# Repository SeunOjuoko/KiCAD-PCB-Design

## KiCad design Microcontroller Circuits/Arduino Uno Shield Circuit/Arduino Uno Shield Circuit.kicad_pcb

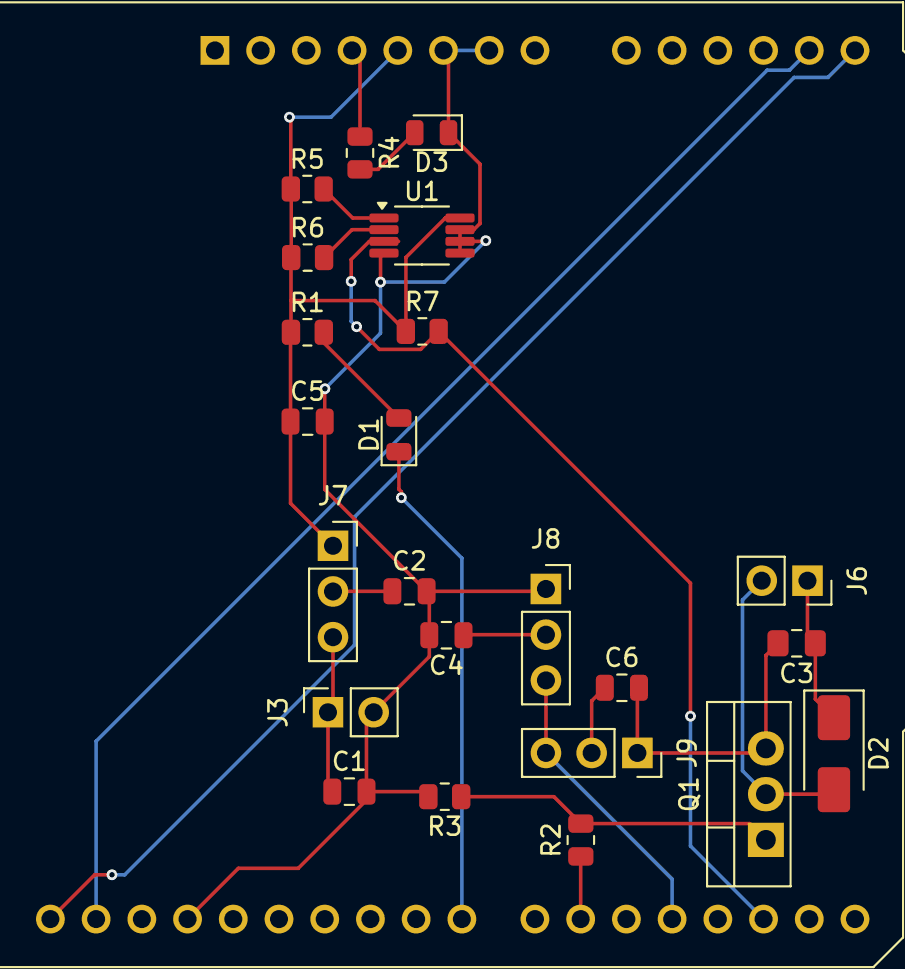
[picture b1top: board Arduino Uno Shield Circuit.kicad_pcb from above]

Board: 2 copper layers, 24 parts (0 on the bottom side), 20 nets.

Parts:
A1: Arduino_UNO_R3
C1, C4, C5, C6: 100nF; C_0805_2012Metric
C2: 100uF; C_0805_2012Metric
C3: 100nF; C_0805_2012Metric_Pad1.18x1.45mm_HandSolder
D1: LED1; LED_0805_2012Metric
D2: D; D_SMA
D3: LED2; LED_0805_2012Metric
J3, J6: Conn_01x02; PinSocket_1x02_P2.54mm_Vertical
J7, J8, J9: Conn_01x03; PinSocket_1x03_P2.54mm_Vertical
Q1: IRF540N; TO-220-3_Vertical
R1, R4: 560R; R_0805_2012Metric
R2: 0R; R_0805_2012Metric
R3, R5, R6, R7: 10K; R_0805_2012Metric
U1: TMP1075DGK; VSSOP-8_3x3mm_P0.65mm

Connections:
+3V3: A1.4 (3V3), R4.1
+5V: A1.5 (+5V), C5.1, J7.1, R1.1, R5.1, R6.1, R7.1, U1.8 (V+)
+V_EXT: C1.1, J3.1, J7.3
/A4: R5.2, U1.1 (SDA)
/A5: R6.2, U1.2 (SCL)
/D2: A1.17 (D2), R7.2, U1.3 (ALERT)
/D4: A1.19 (D4), J8.3, J9.3
/D6: A1.21 (D6), R2.1
/D8: A1.23 (D8), D1.1 (K)
/SCL/A5: A1.14 (SCL/A5), A1.32 (SCL/A5)
/SDA/A4: A1.13 (SDA/A4), A1.31 (SDA/A4)
GND: A1.6 (GND), A1.7 (GND), A1.29 (GND), C1.2, C2.2, C3.2, C4.2, C5.2, C6.2, D3.1 (K), J3.2, J8.1, J9.1, Q1.3 (S), R3.2, U1.4 (GND), U1.5 (A2), U1.6 (A1), U1.7 (A0)
unnamed: D1.2 (A), R1.2
unnamed: D2.2 (A), J6.2, Q1.2 (D)
unnamed: C3.1, D2.1 (K), J6.1
unnamed: D3.2 (A), R4.2
unnamed: C2.1, J7.2
unnamed: C4.1, J8.2
unnamed: C6.1, J9.2
unnamed: Q1.1 (G), R2.2, R3.1

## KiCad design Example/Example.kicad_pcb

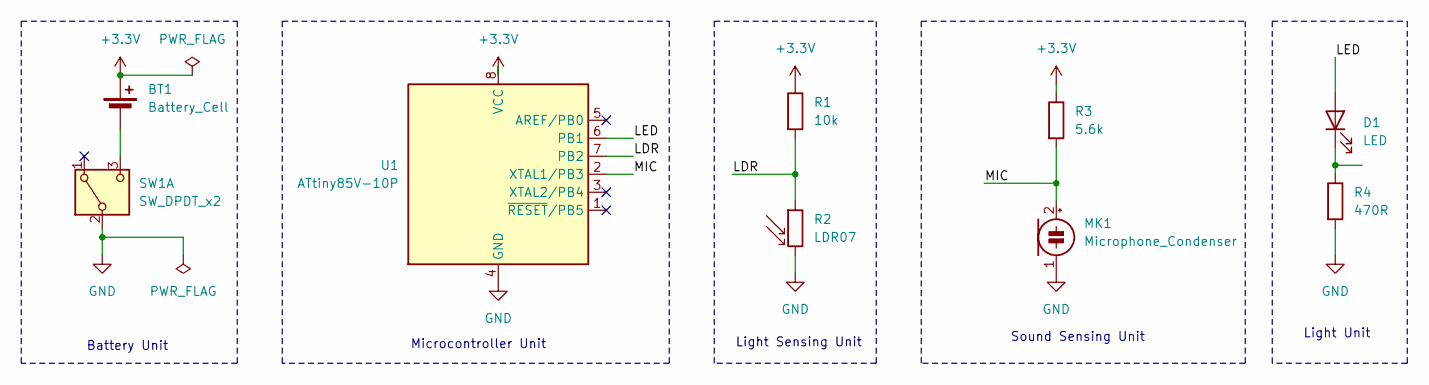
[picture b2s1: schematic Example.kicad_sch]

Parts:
BT1: Battery_Cell; BatteryHolder_ComfortableElectronic_CH273-2450_1x2450
D1: LED; LED_D5.0mm
MK1: Microphone_Condenser; PinHeader_1x02_P2.54mm_Vertical
R1: 10k; R_Axial_DIN0207_L6.3mm_D2.5mm_P15.24mm_Horizontal
R2: LDR07; R_LDR_5.1x4.3mm_P3.4mm_Vertical
R3: 5.6k; R_Axial_DIN0207_L6.3mm_D2.5mm_P15.24mm_Horizontal
R4: 470R; R_Axial_DIN0207_L6.3mm_D2.5mm_P15.24mm_Horizontal
SW1: SW_DPDT_x2; SW_CK_JS202011AQN_DPDT_Angled
U1: ATtiny85V-10P; DIP-8_W7.62mm

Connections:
+3.3V: BT1.1 (+), R1.1, R3.1, U1.8 (VCC)
/LDR: R1.2, R2.1, U1.7 (PB2)
/LED: D1.2 (A), U1.6 (PB1)
/MIC: MK1.2 (+), R3.2, U1.2 (XTAL1/PB3)
GND: MK1.1 (-), R2.2, R4.2, SW1.2 (B), U1.4 (GND)
unnamed: BT1.2 (-), SW1.3 (C)
unnamed: D1.1 (K), R4.1

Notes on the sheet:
Sound Sensing Unit
Light Sensing Unit
Battery Unit
Microcontroller Unit
Light Unit

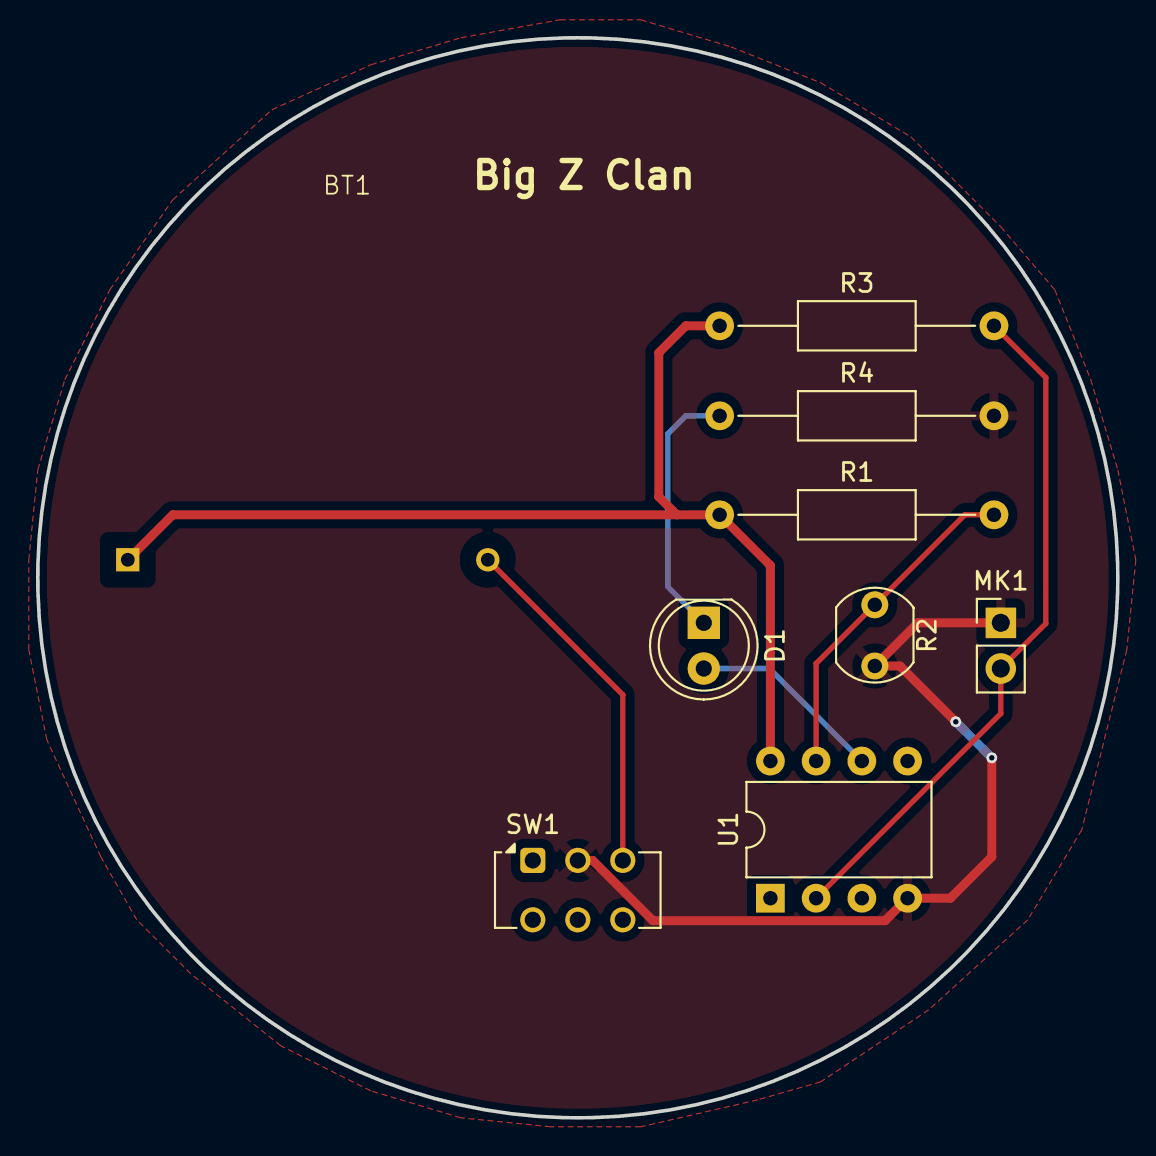
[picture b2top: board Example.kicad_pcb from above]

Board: 2 copper layers, 60.0 x 60.0 mm, 9 parts (0 on the bottom side), 7 nets.

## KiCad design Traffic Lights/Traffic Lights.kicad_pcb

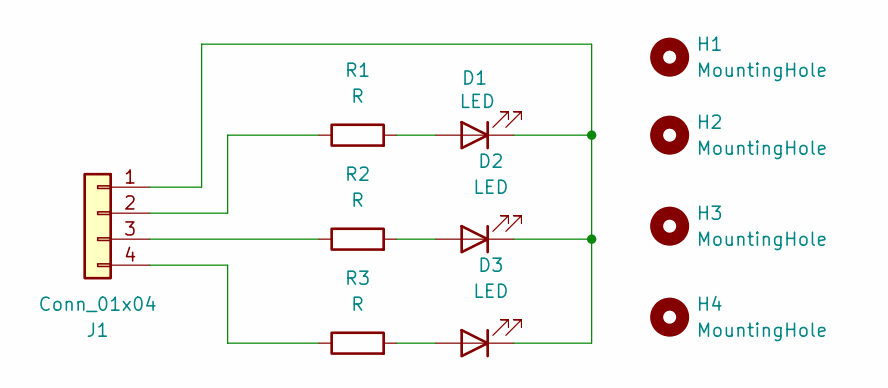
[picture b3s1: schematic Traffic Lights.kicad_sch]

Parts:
D1, D2, D3: LED; LED_D3.0mm
H1, H2, H3, H4: MountingHole; MountingHole_2.5mm_Pad
J1: Conn_01x04; PinHeader_1x04_P2.54mm_Horizontal
R1, R2, R3: R; R_Axial_DIN0204_L3.6mm_D1.6mm_P5.08mm_Vertical

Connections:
unnamed: D1.2 (A), R1.2
unnamed: D1.1 (K), D2.1 (K), D3.1 (K), J1.1
unnamed: D2.2 (A), R2.2
unnamed: D3.2 (A), R3.2
unnamed: J1.2, R1.1
unnamed: J1.3, R2.1
unnamed: J1.4, R3.1

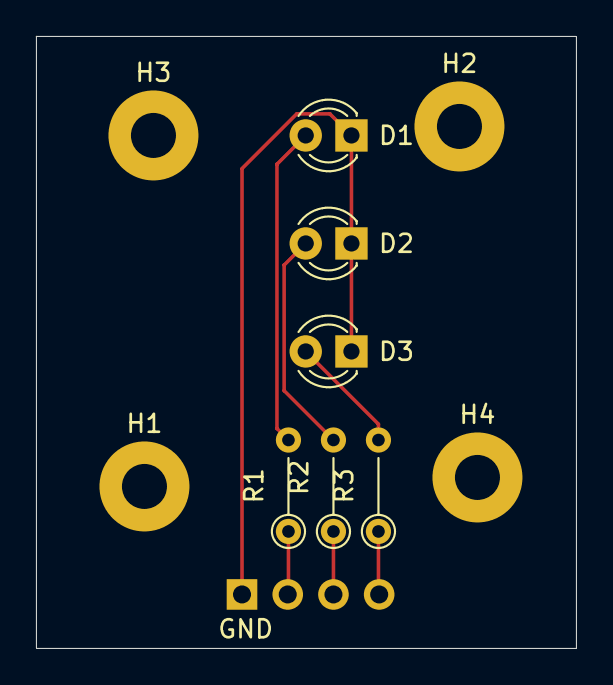
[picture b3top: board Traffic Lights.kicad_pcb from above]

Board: 2 copper layers, 30.0 x 34.0 mm, 11 parts (1 on the bottom side), 7 nets.

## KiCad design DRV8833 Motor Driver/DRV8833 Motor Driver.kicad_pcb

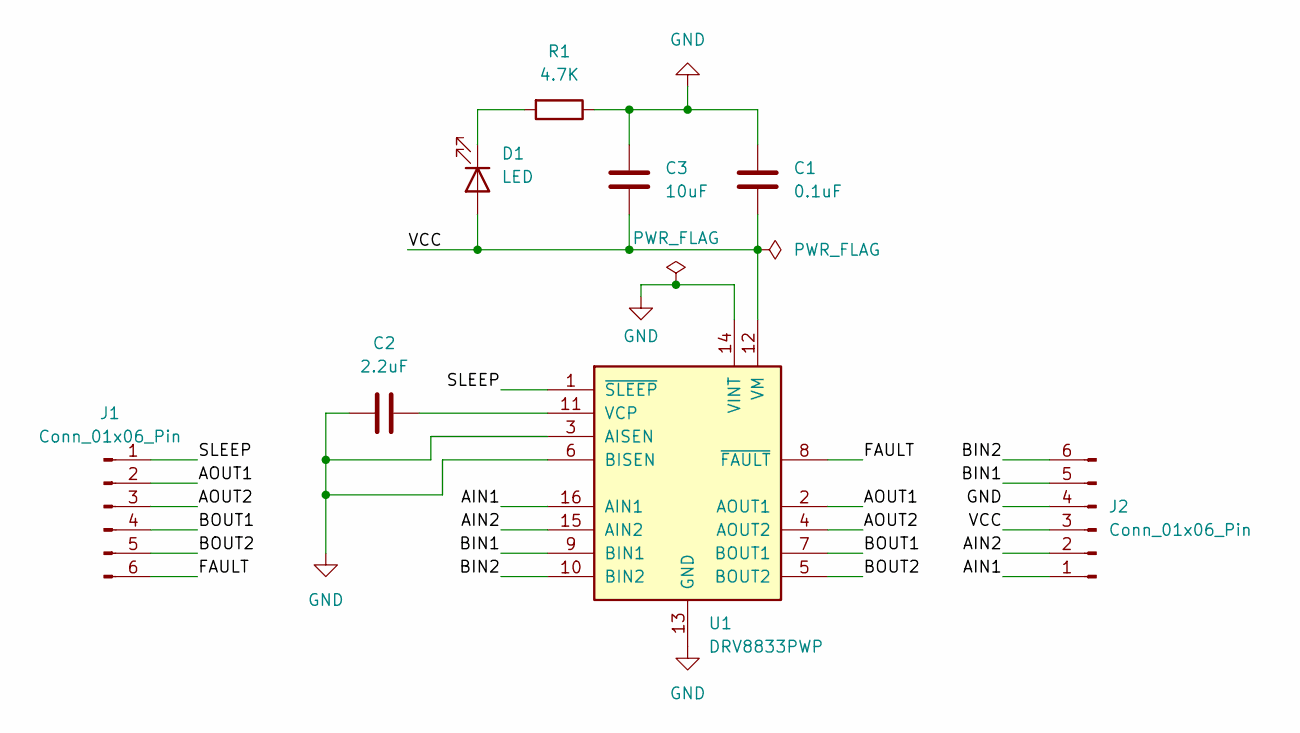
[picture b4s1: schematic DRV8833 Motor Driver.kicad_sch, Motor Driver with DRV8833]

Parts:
C1: 0.1uF; C_0805_2012Metric
C2: 2.2uF; C_0805_2012Metric
C3: 10uF; CP_EIA-6032-20_AVX-F
D1: LED; LED_0805_2012Metric
J1, J2: Conn_01x06_Pin; PinHeader_1x06_P2.54mm_Vertical
R1: 4.7K; R_0805_2012Metric
U1: DRV8833PWP; HTSSOP-16-1EP_4.4x5mm_P0.65mm_EP3.4x5mm_Mask2.46x2.31mm_The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

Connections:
/AIN1: J2.1, U1.16 (AIN1)
/AIN2: J2.2, U1.15 (AIN2)
/AOUT1: J1.2, U1.2 (AOUT1)
/AOUT2: J1.3, U1.4 (AOUT2)
/BIN1: J2.5, U1.9 (BIN1)
/BIN2: J2.6, U1.10 (BIN2)
/BOUT1: J1.4, U1.7 (BOUT1)
/BOUT2: J1.5, U1.5 (BOUT2)
/FAULT: J1.6, U1.8 (~FAULT)
/SLEEP: J1.1, U1.1 (~SLEEP)
/VCC: C1.2, C3.2, D1.2 (A), J2.3, U1.12 (VM)
GND: C1.1, C2.1, C3.1, J2.4, R1.1, U1.3 (AISEN), U1.6 (BISEN), U1.13 (GND), U1.14 (VINT), U1.17 (GND)
unnamed: D1.1 (K), R1.2
unnamed: C2.2, U1.11 (VCP)

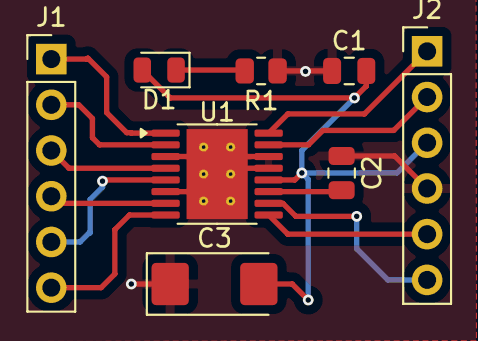
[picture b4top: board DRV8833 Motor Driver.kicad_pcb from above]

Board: 2 copper layers, 8 parts (0 on the bottom side), 14 nets.

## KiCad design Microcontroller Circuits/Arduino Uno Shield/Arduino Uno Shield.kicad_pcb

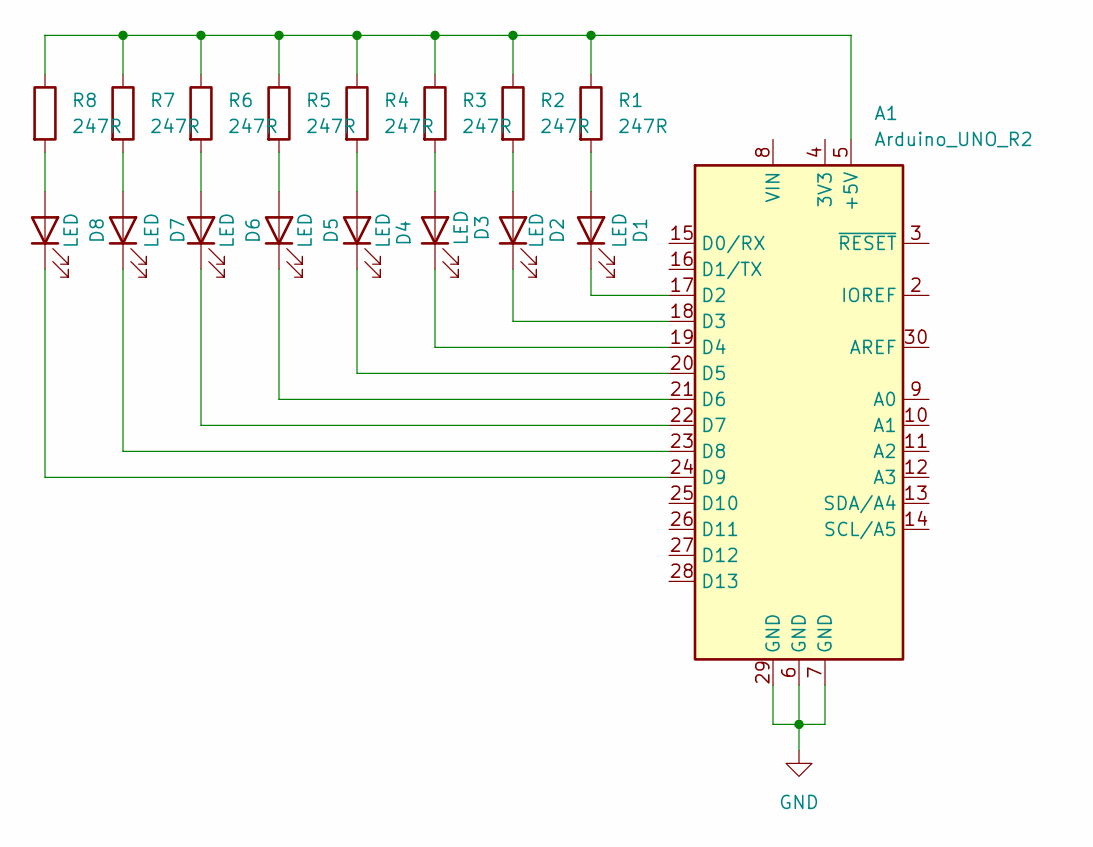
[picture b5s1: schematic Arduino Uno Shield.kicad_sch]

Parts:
A1: Arduino_UNO_R2
D1, D2, D3, D4, D5, D6, D7, D8: LED; LED_0805_2012Metric
R1, R2, R3, R4, R5, R6, R7, R8: 247R; R_0603_1608Metric

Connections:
GND: A1.6 (GND), A1.7 (GND), A1.29 (GND)
unnamed: A1.5 (+5V), R1.1, R2.1, R3.1, R4.1, R5.1, R6.1, R7.1, R8.1
unnamed: A1.17 (D2), D1.1 (K)
unnamed: A1.18 (D3), D2.1 (K)
unnamed: A1.19 (D4), D3.1 (K)
unnamed: A1.20 (D5), D4.1 (K)
unnamed: A1.21 (D6), D5.1 (K)
unnamed: A1.22 (D7), D6.1 (K)
unnamed: A1.23 (D8), D7.1 (K)
unnamed: A1.24 (D9), D8.1 (K)
unnamed: D1.2 (A), R1.2
unnamed: D2.2 (A), R2.2
unnamed: D3.2 (A), R3.2
unnamed: D4.2 (A), R4.2
unnamed: D5.2 (A), R5.2
unnamed: D6.2 (A), R6.2
unnamed: D7.2 (A), R7.2
unnamed: D8.2 (A), R8.2

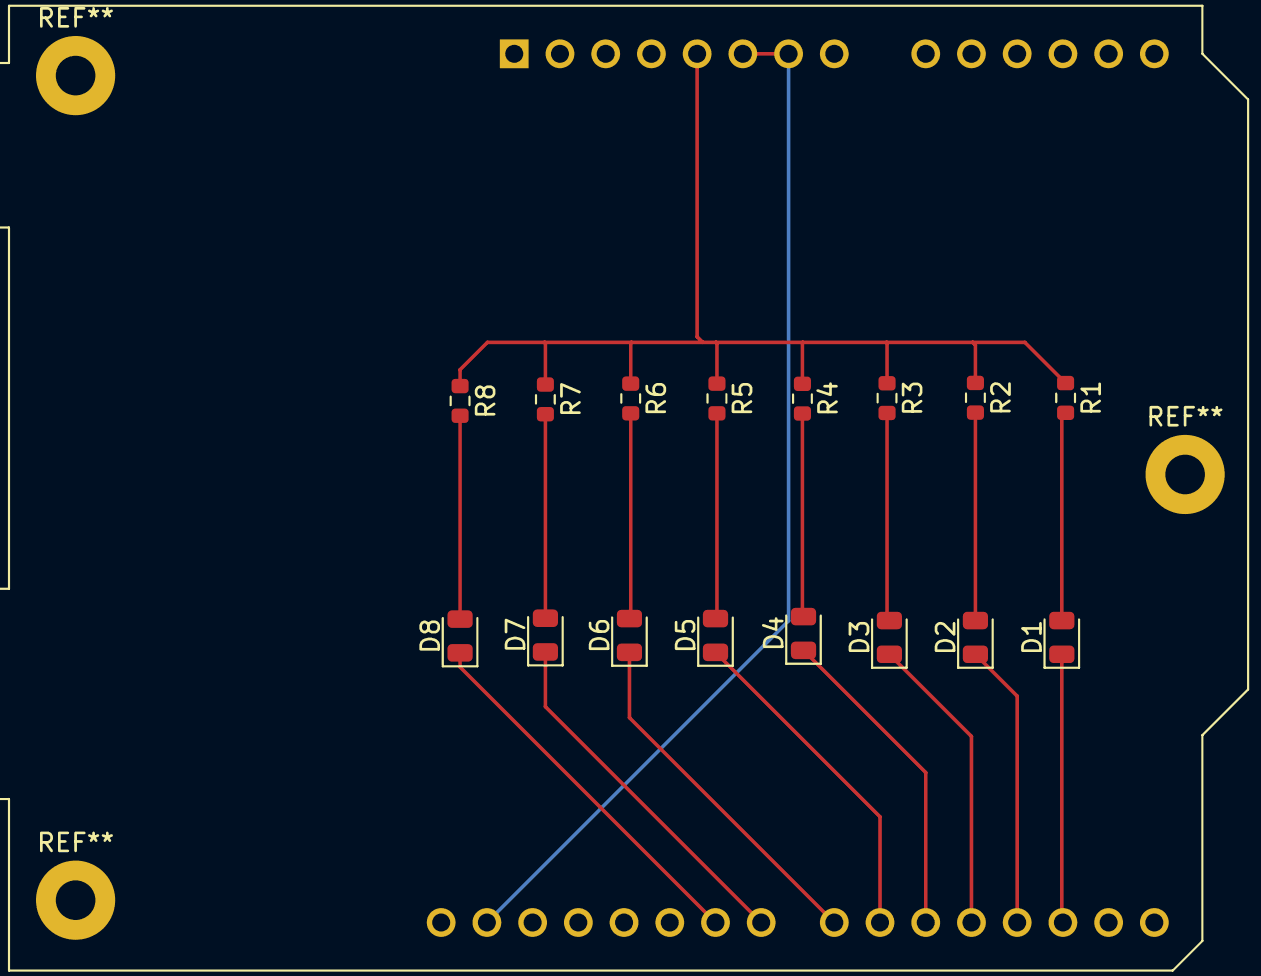
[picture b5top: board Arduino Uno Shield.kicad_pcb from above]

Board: 2 copper layers, 17 parts (0 on the bottom side), 18 nets.

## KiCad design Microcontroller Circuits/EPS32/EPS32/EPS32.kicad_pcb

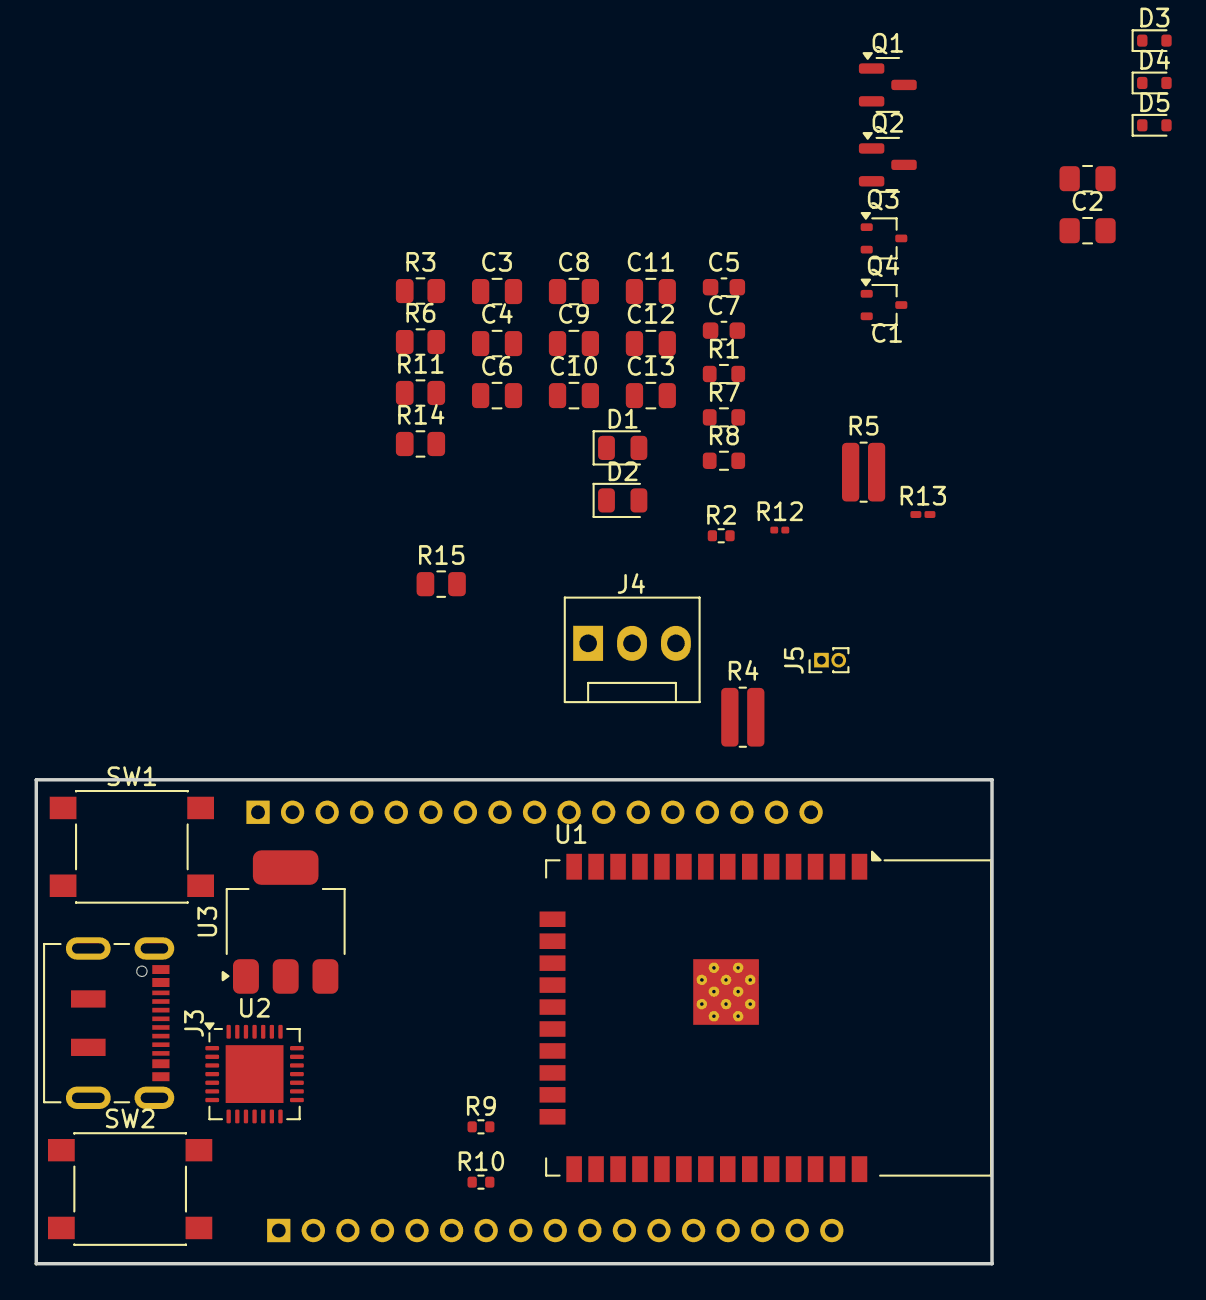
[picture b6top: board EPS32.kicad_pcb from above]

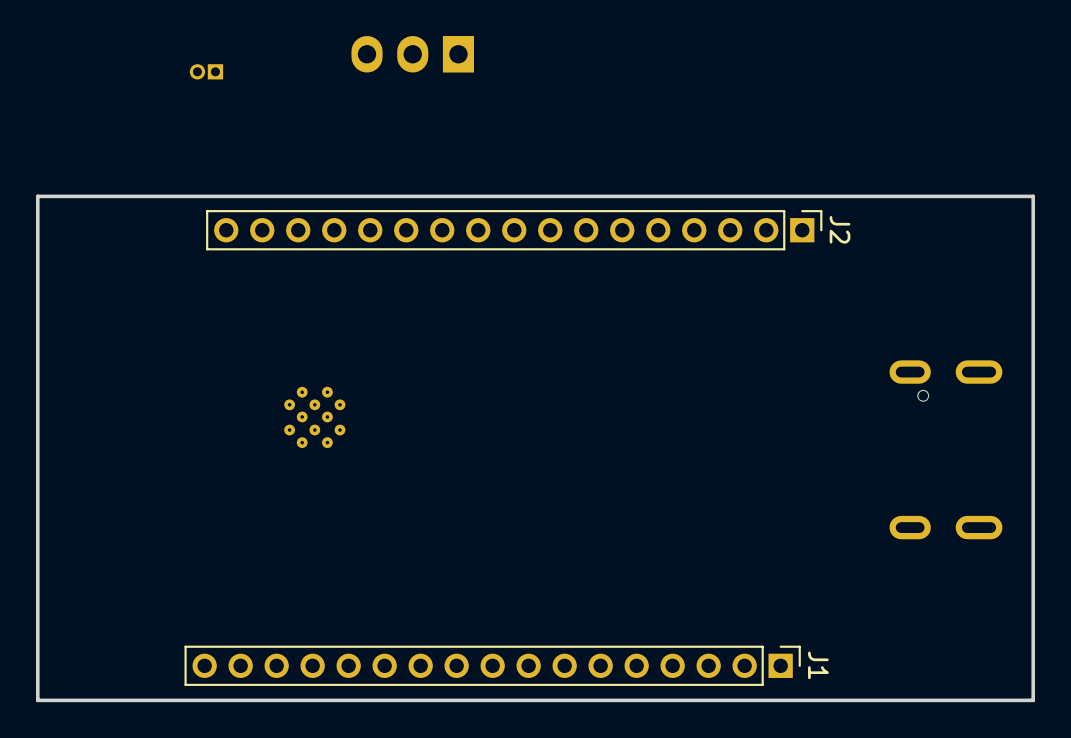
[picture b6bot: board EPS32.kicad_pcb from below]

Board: 2 copper layers, 55.3 x 28.0 mm, 47 parts (2 on the bottom side), 20 nets, no tracks yet.

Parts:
C1, C2: 10uF; C_0805_2012Metric_Pad1.18x1.45mm_HandSolder
C3, C4, C6, C8, C9, C10, C11, C12, C13: 100nF; C_0805_2012Metric
C5, C7: 4.7uF; C_0603_1608Metric
D1, D2: GREEN LED; LED_0805_2012Metric
D3, D4, D5: D_TVS; D_SOD-523
J1, J2: Conn_01x17; PinHeader_1x17_P2.00mm_Vertical
J3: Socket Type Micro B 2.0 USB; USB_C_Receptacle_JAE_DX07S016JA1R1500
J4: Conn_01x03; FanPinHeader_1x03_P2.54mm_Vertical
J5: Conn_01x02; PinHeader_1x02_P1.00mm_Vertical
Q1, Q2: 2N7002; SOT-23
Q3, Q4: BC818W; SOT-323_SC-70
R1: 5.1K; R_0603_1608Metric
R2: 560R; R_0402_1005Metric
R3, R6, R11, R14, R15: 10K; R_0805_2012Metric
R4, R5: 1K; R_0612_1632Metric
R7: 22.1K; R_0603_1608Metric
R8: 47.5K; R_0603_1608Metric
R9, R10: 22R; R_0402_1005Metric
R12: 0R; R_0201_0603Metric
R13: 0R; R_0201_0603Metric_Pad0.64x0.40mm_HandSolder
SW1, SW2: SW_Push_Dual_x2; SW_SPST_PTS645
U1: ESP32-WROOM-32E; ESP32-WROOM-32D
U2: CP2102N-Axx-xQFN28; QFN-28-1EP_5x5mm_P0.5mm_EP3.35x3.35mm
U3: AMS1117CS-3.3; SOT-223

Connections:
+3.3V: C2.1, C5.1, C6.1, C7.1, C8.1, C9.1, C11.1, J1.2, J2.1, J5.1, R1.1, R2.1, R5.1, R11.1, U1.2 (VDD), U2.6 (VDD), U2.7 (VREGIN), U3.2 (VO), U3.4 (TAB)
+5V: C1.1, J4.2, U3.3 (VI)
GND: C1.2, C2.2, C3.2, C4.2, C5.2, C6.2, C7.2, C8.2, C9.2, C10.2, C11.2, C12.2, C13.2, D1.1 (K), D3.1 (A1), D4.1 (A1), D5.1 (A1), J1.1, J1.4, J1.15, J2.2, J2.4, J2.8, J2.13, J2.15, J2.16, Q1.2 (S), Q2.2 (S), R3.2, R6.2, R8.2, SW1.1 (C), SW2.1 (C), U1.1 (GND), U1.15 (GND), U1.38 (GND), U1.39 (GND), U2.3 (GND), U2.29 (GND), U3.1 (GND)
unnamed: D1.2 (A), R1.2
unnamed: D2.2 (A), R2.2
unnamed: C3.1, D3.2 (A2)
unnamed: D4.2 (A2), Q2.3 (D)
unnamed: D5.2 (A2), Q1.3 (D)
unnamed: C10.1, J1.17
unnamed: C4.1, J5.2, Q1.1 (G), Q2.1 (G), R3.1, R4.1
unnamed: Q3.1 (B), R14.1
unnamed: Q3.2 (E), R15.2
unnamed: Q4.1 (B), R15.1
unnamed: Q4.3 (C), R14.2
unnamed: C12.1, R11.2, SW1.2 (D)
unnamed: C13.1, SW2.2 (D)
unnamed: R9.2, R10.2, U1.25 (IO0)
unnamed: R7.2, R8.1, U2.8 (VBUS)
unnamed: R5.2, U2.9 (~RST)
unnamed: R6.1, U2.11 (~SUSPEND)

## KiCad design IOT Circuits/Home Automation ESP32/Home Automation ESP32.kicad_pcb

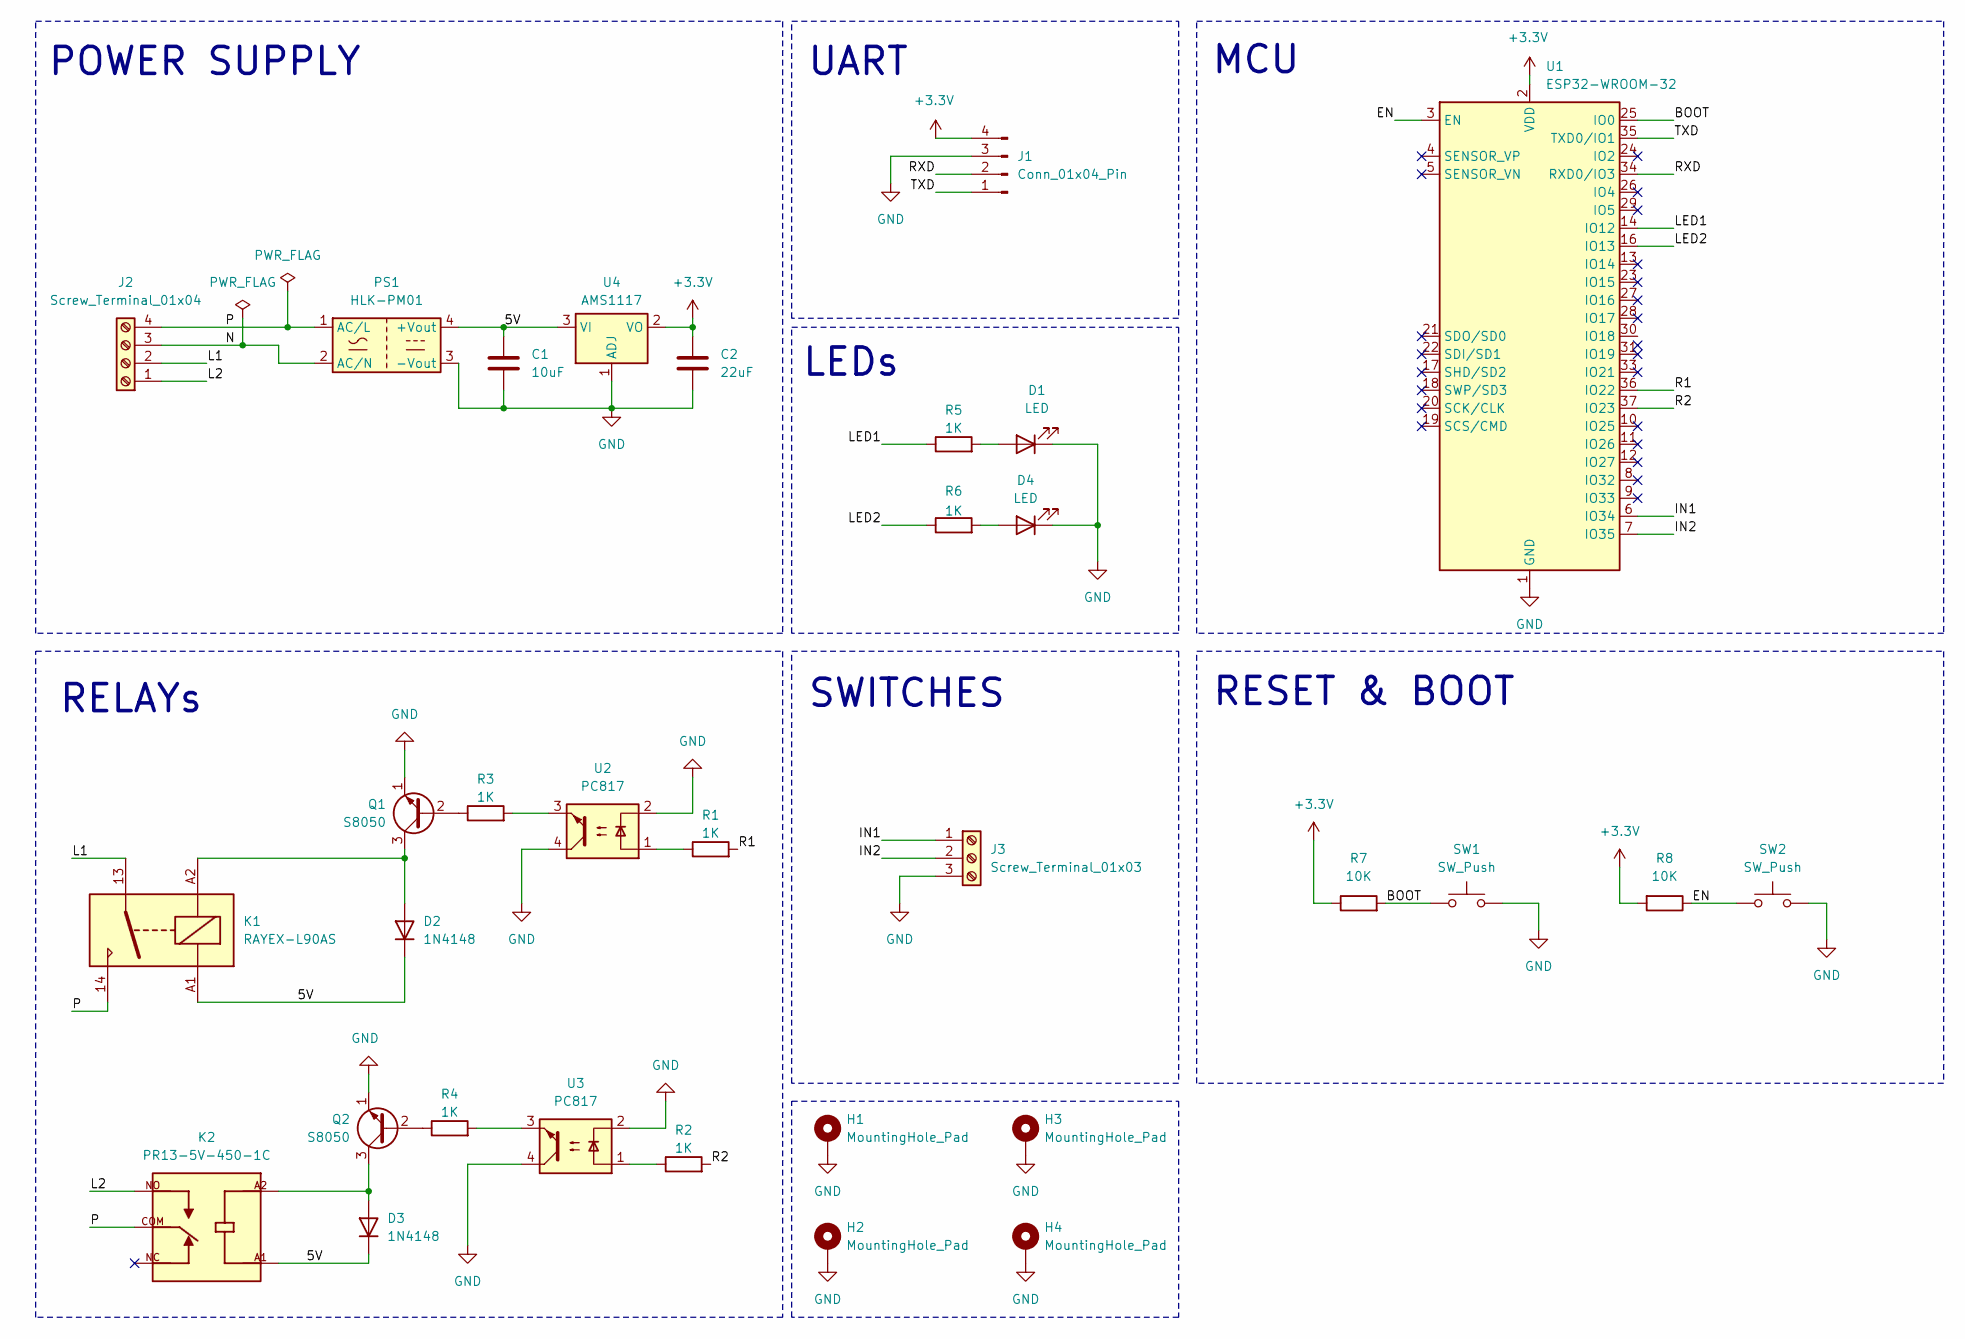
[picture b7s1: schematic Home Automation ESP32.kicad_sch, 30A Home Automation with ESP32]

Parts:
C1: 10uF; C_0805_2012Metric
C2: 22uF; C_0805_2012Metric
D1, D4: LED; LED_0805_2012Metric
D2, D3: 1N4148; D_DO-35_SOD27_P7.62mm_Horizontal
H1, H2, H3, H4: MountingHole_Pad; MountingHole_2.7mm_M2.5_Pad_Via
J1: Conn_01x04_Pin; PinHeader_1x04_P2.54mm_Vertical
J2: Screw_Terminal_01x04; TerminalBlock_bornier-4_P5.08mm
J3: Screw_Terminal_01x03; TerminalBlock_bornier-3_P5.08mm
K1: RAYEX-L90AS; Relay_SPST_RAYEX-L90AS
K2: PR13-5V-450-1C; RELAY_PR13-5V-450-1C; PARTREV 1.0
PS1: HLK-PM01; Converter_ACDC_Hi-Link_HLK-PMxx
Q1, Q2: S8050; TO-92_Inline
R1, R2, R3, R4, R5, R6: 1K; R_0805_2012Metric
R7, R8: 10K; R_0805_2012Metric
SW1, SW2: SW_Push; SW_PUSH_6mm
U1: ESP32-WROOM-32
U2, U3: PC817; DIP-4_W7.62mm
U4: AMS1117; SOT-223-3_TabPin2

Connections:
+3.3V: C2.1, J1.4, R7.1, R8.2, U1.2 (VDD), U4.2 (VO)
/5V: C1.1, D2.1 (K), D3.1 (K), K1.A1, K2.A1, PS1.4 (+Vout), U4.3 (VI)
/BOOT: R7.2, SW1.1, U1.25 (IO0)
/EN: R8.1, SW2.1, U1.3 (EN)
/IN1: J3.1, U1.6 (IO34)
/IN2: J3.2, U1.7 (IO35)
/L1: J2.2, K1.13
/L2: J2.1, K2.NO
/LED1: R5.1, U1.14 (IO12)
/LED2: R6.1, U1.16 (IO13)
/N: J2.3, PS1.2 (AC/N)
/P: J2.4, K1.14, K2.COM, PS1.1 (AC/L)
/R1: R1.2, U1.36 (IO22)
/R2: R2.2, U1.37 (IO23)
/RXD: J1.2, U1.34 (RXD0/IO3)
/TXD: J1.1, U1.35 (TXD0/IO1)
GND: C1.2, C2.2, D1.1 (K), D4.1 (K), H1.1, H2.1, H3.1, H4.1, J1.3, J3.3, PS1.3 (-Vout), Q1.1 (E), Q2.1 (E), SW1.2, SW2.2, U1.1 (GND), U1.15 (GND), U1.38 (GND), U1.39 (GND), U2.2, U2.4, U3.2, U3.4, U4.1 (ADJ)
unnamed: D1.2 (A), R5.2
unnamed: D2.2 (A), K1.A2, Q1.3 (C)
unnamed: D3.2 (A), K2.A2, Q2.3 (C)
unnamed: D4.2 (A), R6.2
unnamed: Q1.2 (B), R3.1
unnamed: Q2.2 (B), R4.1
unnamed: R1.1, U2.1
unnamed: R2.1, U3.1
unnamed: R3.2, U2.3
unnamed: R4.2, U3.3

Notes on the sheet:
POWER SUPPLY
LEDs
RESET & BOOT
SWITCHES
RELAYs
UART
MCU

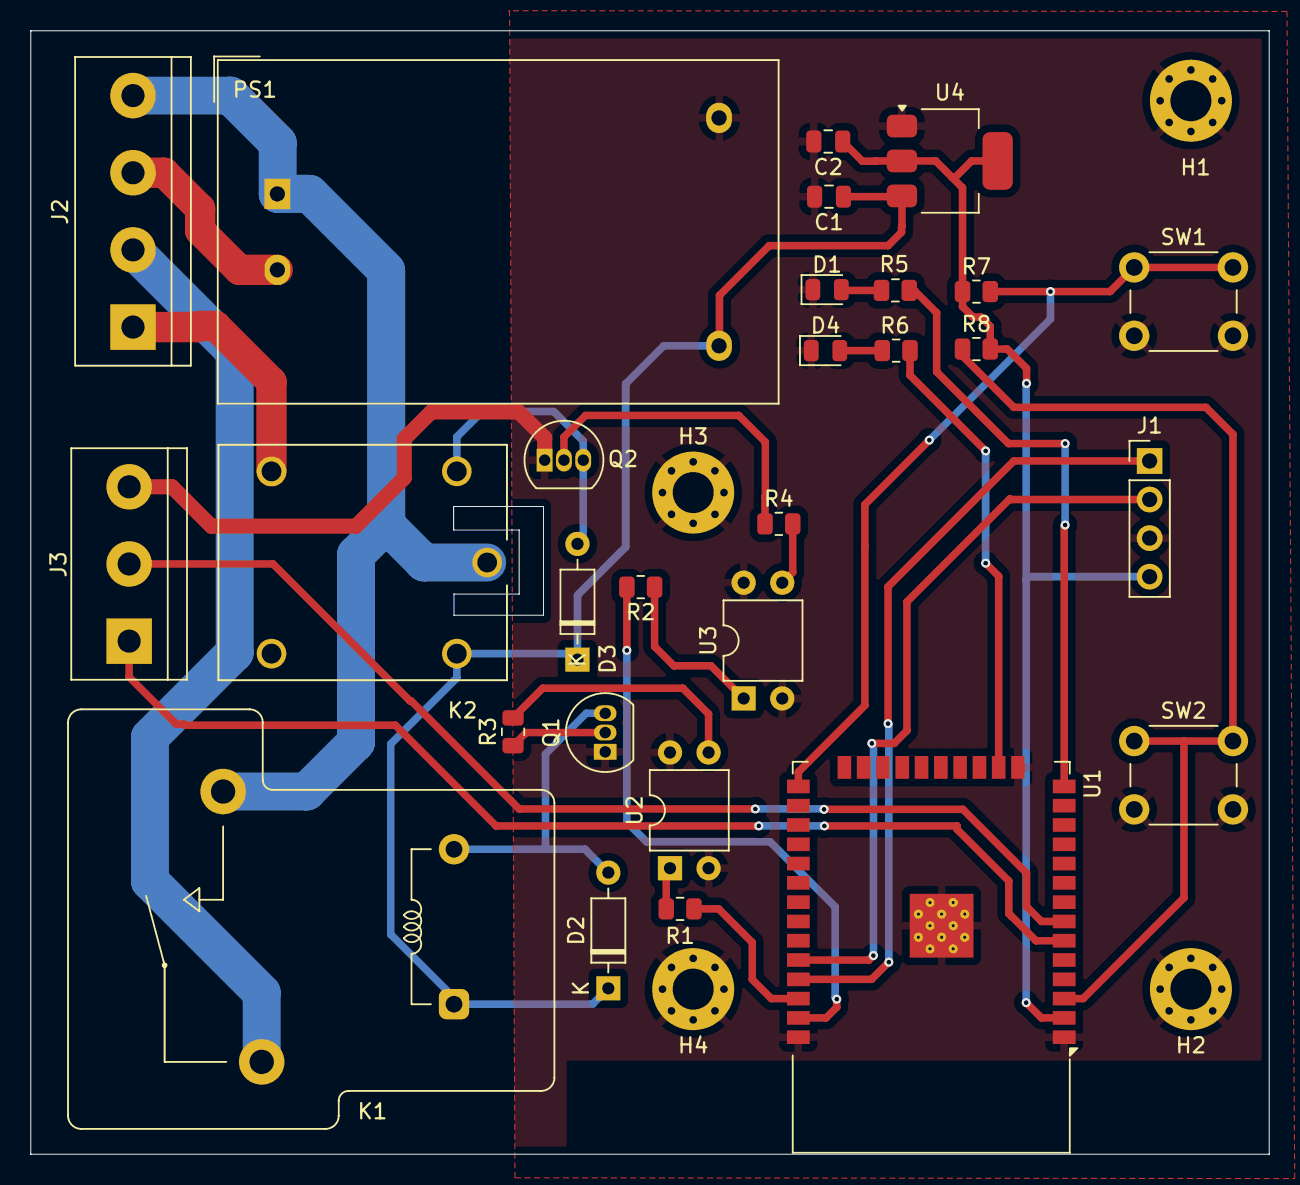
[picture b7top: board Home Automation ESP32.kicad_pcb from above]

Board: 2 copper layers, 81.5 x 74.0 mm, 32 parts (0 on the bottom side), 27 nets.
